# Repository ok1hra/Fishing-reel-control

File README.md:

# Fishing-reel-control 

KiCad PCB layout

* [Schematics](KiCad-PCB/Ali-FM.pdf)
* [Interactive bom!](http://htmlpreview.github.io/?https://github.com/ok1hra/Fishing-reel-control/blob/master/KiCad-PCB/ibom.html)
* [STEP 3D model of PCB](KiCad-PCB/Ali-FM.step)
* [Firmware](https://github.com/ok1hra/Fishing-reel-control/tree/master/Arduino_firmware)

## Functionality
* Show battery voltage at start up
* LCD show counter, speed in metre unit + battery voltage bargraph
* Capacitive button sensor for up, down an reset with LED light feedback
* Ambient light sensor automaticaly adjust LCD backlight
* After 20 seconds storage last value, for recovery after restart power
* 12V DC power input
* Counter input for two hall effect switch
* Waterproof 3D printed case (PET)

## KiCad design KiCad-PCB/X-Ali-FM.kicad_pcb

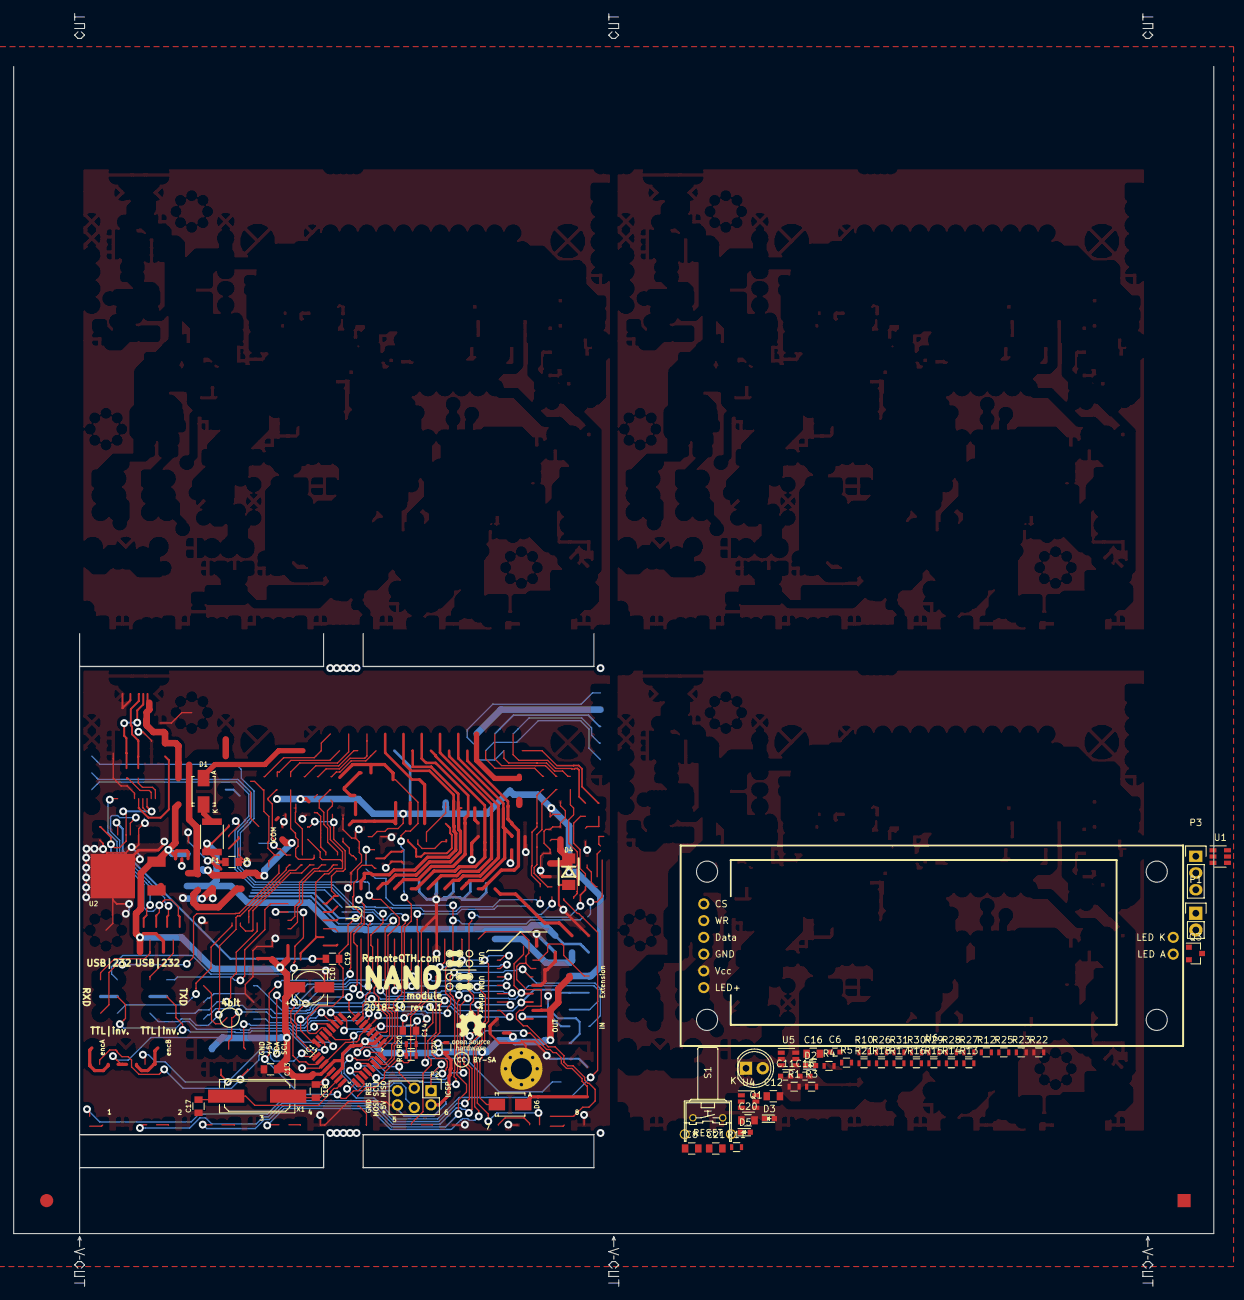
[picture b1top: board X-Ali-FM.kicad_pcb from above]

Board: 2 copper layers, 182.0 x 193.0 mm, 62 parts (0 on the bottom side), 39 nets.

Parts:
C6, C11, C15: 100n; C_0603
C8, C12, C16: 22n; C_0805
C9, C13, C14, C19: 100n; C_0805
C10: 33u; c_elec_5x5.7
C17, C18: 22p; C_0805
C20, C21: 10n; C_0805
D1, D6: SS14-DC; SMA_Standard
D2, D3, D5: GRN; LED_0603
D4: 6V*; DO-214AC
F1: PTC; C_1812
IC1: ATMEGA328P-A; TQFP-32_7x7mm_Pitch0.8mm
P1: CONN_01X02; Pin_Header_Straight_1x02
P2: CONN_3X2; Pin_Header_Straight_2x03
P3: Hall sensor; Pin_Header_Straight_1x03
P8: CONN_1; MountingHole_3.2mm_M3_Pad_Via
Q1: Q_Photo_NPN; LED-5MM
Q3: MMBF170; SOT-23
R1, R10, R19, R20, R24, R27, R28: 10k; R_0603
R3, R14, R18: 0R; R_0603
R4, R11, R12, R15, R21, R25, R26: 1k; R_0603
R5, R16, R22: 0R*; R_0603
R13, R17, R23: 3k6; R_0603
R29, R31: 100R; R_0603
R30: 100k; R_0603
S1: RESET; TACT-90
U1, U4, U5: AT42QT1011-TSHR; SOT-23-6
U2: LF50CDT; D-Pak_TO252AA
U6: LCD-6x1-HT1621
X1: 16MHz; Q_49U3HMS

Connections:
+5V: C6.2, C10.1, C11.2, C13.1, C15.2, D4.1, D6.1, IC1.4, IC1.6, IC1.18, P2.2, R1.1, R5.2, R16.2, R19.1, R20.1, R22.2, R24.2, R27.2, R28.2, U1.5, U2.3, U4.5, U5.5, U6.5
/A6: IC1.19, R10.1, R11.2
/A7: IC1.22, Q1.1, R1.2
/D2: IC1.32, R25.2
/D3: IC1.1, R26.2
/D4: IC1.2, R21.2, U5.1
/D5: IC1.9, R29.2
/D7: IC1.11, U6.3
/D8: IC1.12, R4.2, U1.1
/D9: IC1.13, R15.2, U4.1
/D11(MOSI): IC1.15, P2.4
/D12(MISO): IC1.16, P2.1, U6.2
/D13(SCLK): IC1.17, P2.3, U6.1
/RES: C19.2, D6.2, IC1.29, P2.5, R24.1, S1.2
GND: C6.1, C9.1, C10.2, C11.1, C13.2, C14.1, C15.1, C17.2, C18.2, C20.1, C21.1, D2.1, D3.1, D4.2, D5.1, IC1.3, IC1.5, IC1.21, P1.2, P2.6, P3.2, P8.1, Q1.2, Q3.2, R3.1, R12.1, R14.1, R18.1, R30.2, S1.1, S1.3, U1.2, U2.4, U4.2, U5.2, U6.4
unnamed: C8.1, R13.2, U1.3
unnamed: C8.2, U1.4
unnamed: C9.2, F1.2, R10.2, U2.1
unnamed: C12.1, R17.2, U4.3
unnamed: C12.2, U4.4
unnamed: C14.2, IC1.20, R19.2, R20.2
unnamed: C16.1, R23.2, U5.3
unnamed: C16.2, U5.4
unnamed: C17.1, IC1.8, X1.1
unnamed: C18.1, IC1.7, X1.2
unnamed: C20.2, P3.1, R25.1, R27.1
unnamed: C21.2, P3.3, R26.1, R28.1
unnamed: D1.1, F1.1
unnamed: D1.2, P1.1
unnamed: D2.2, R4.1
unnamed: D3.2, R15.1
unnamed: D5.2, R21.1
unnamed: Q3.1, R29.1, R30.1
unnamed: Q3.3, R31.1
unnamed: R3.2, R5.1, U1.6
unnamed: R11.1, R12.2
unnamed: R14.2, R16.1, U4.6
unnamed: R18.2, R22.1, U5.6
unnamed: R31.2, U6.7
